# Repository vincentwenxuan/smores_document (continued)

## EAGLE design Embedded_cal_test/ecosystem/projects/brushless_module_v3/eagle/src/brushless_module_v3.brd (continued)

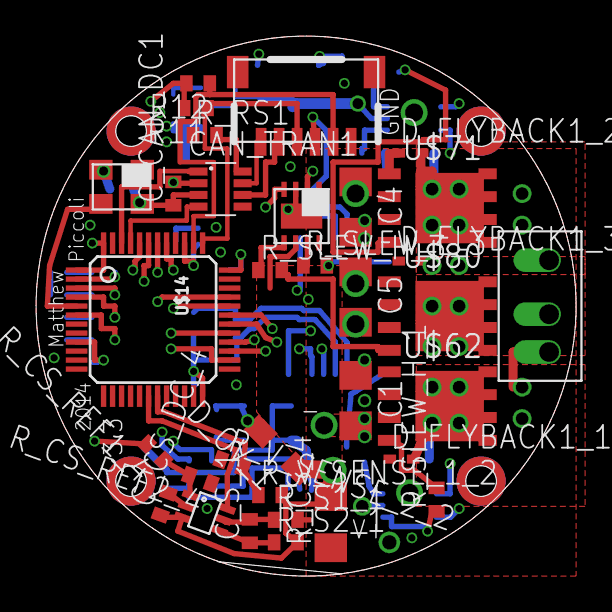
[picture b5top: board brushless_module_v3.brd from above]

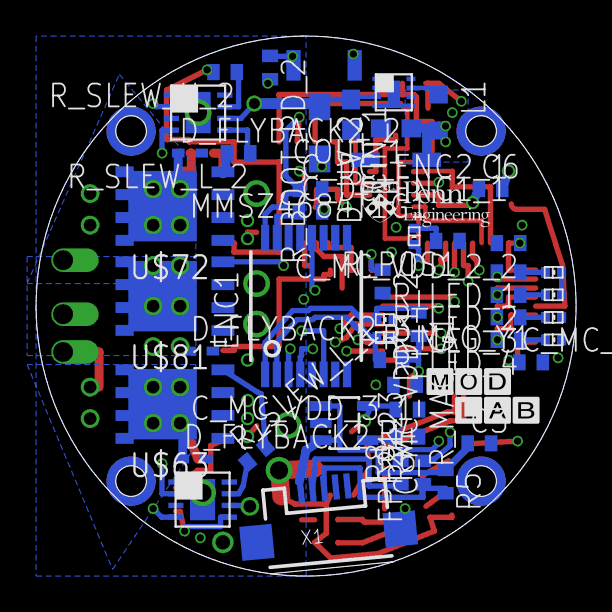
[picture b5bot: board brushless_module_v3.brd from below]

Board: 4 copper layers, 30.0 x 30.0 mm, 84 parts (51 on the bottom side), 63 nets.

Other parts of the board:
U$6: MODLAB
U$12: PENN_ENGINEERING

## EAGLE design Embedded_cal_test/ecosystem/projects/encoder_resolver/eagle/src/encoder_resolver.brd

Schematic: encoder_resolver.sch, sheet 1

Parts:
C_MC_VDDA_1: 100nF; C0603
C_MC_VDD_1_1: 4.7uF; C0603
C_MC_VDD_2_1: 100nF; C0603
IC7: STM32F373CC; LQFP48
LED1, LED2, LED3, LED4: LEDCHIPLED_0603; CHIPLED_0603
OSC1: FOX924B; 4-SMD_5X3.2
R_BOOT_PU_1: 1k; R0603
R_LED_1, R_LED_3, R_LED_4, R_LED_5: 1k; R0603
R_NRST_PU_1: 1k; R0603
R_V_SENSE_1_1: 88.7kΩ; R0603
R_V_SENSE_2_1: 20kΩ; R0603
SW1: B3U

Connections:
16MHZ_3V3: IC7.5 (PF0-OSC_IN-I2C2SDA+), OSC1.P$3 (OUTPUT)
+3V3: C_MC_VDDA_1.1, C_MC_VDD_1_1.1, C_MC_VDD_2_1.1, IC7.1 (VBAT), IC7.9 (VDDA-VREF+), IC7.17 (VDD_2), IC7.24 (VDDSD), IC7.25 (VREFSD), IC7.48 (VDD_1), LED1.A, LED2.A, LED3.A, LED4.A, OSC1.P$4 (VCC), R_NRST_PU_1.1, SW1.P$2; also elsewhere on the board
BOOT0_1: IC7.44 (BOOT0), R_BOOT_PU_1.1, SW1.P$1
D+1: IC7.33 (PA12-USART1RTS/USBDP/SPI1SCK); also elsewhere on the board
D-1: IC7.32 (PA11-USART1CTS/USBDM/SPI2NSS/SPI1NSS); also elsewhere on the board
ENC_CLK_1: IC7.11 (PA1-USART2RTS/ADC1/SPI3SCK/TIM2CH2); also elsewhere on the board
ENC_CSN_1: IC7.10 (PA0-USART2CTS/ADC0); also elsewhere on the board
ENC_MISO_1: IC7.12 (PA2-USART2TX/ADC2/SPI3MISO/TIM2CH3); also elsewhere on the board
E_R1-R2_MICRO: IC7.16 (PA6-SPI1MISO/ADC6/TIM3CH1); also elsewhere on the board
E_S1-S3_MICRO: IC7.14 (PA4-SPI1NSS/ADC4/SPI3NSS/USART2CK); also elsewhere on the board
E_S2-S4_MICRO: IC7.15 (PA5-SPI1SCK/ADC5); also elsewhere on the board
GND: C_MC_VDDA_1.2, C_MC_VDD_1_1.2, C_MC_VDD_2_1.2, IC7.8 (VSSA-VREF-), IC7.23 (VSSD-VREFSD-), IC7.47 (VSS_1), OSC1.P$2 (GND), R_BOOT_PU_1.2, R_V_SENSE_2_1.1; also elsewhere on the board
INDEX1: IC7.6 (PF1-OSC_OUT-I2C2SCL+); also elsewhere on the board
MAGDEC1: IC7.41 (PB5-SPI1MOSI/SPI3MOSI); also elsewhere on the board
unnamed: LED1.C, R_LED_1.2
unnamed: IC7.18 (PB0-ADC8/SPI1MOSI/TIM3CH3), R_V_SENSE_1_1.1, R_V_SENSE_2_1.2
unnamed: IC7.38 (PA15-I2C1SCL+), R_LED_1.1
unnamed: LED2.C, R_LED_3.2
unnamed: IC7.37 (PA14-I2C1SDA+), R_LED_3.1
unnamed: LED4.C, R_LED_4.2
unnamed: LED3.C, R_LED_5.2
unnamed: IC7.29 (PA8-USART1CK/SPI2SCK/MCO), R_LED_4.1
unnamed: IC7.30 (PA9-USART1TX/SPI2MISO), R_LED_5.1
NRST_1: IC7.7 (NRST), R_NRST_PU_1.2
POS_PWM1: IC7.13 (PA3-USART2RX/ADC3/SPI3MOSI/TIM2CH4); also elsewhere on the board
QEPA1: IC7.42 (PB6-I2C1SCL+); also elsewhere on the board
QEPB1: IC7.43 (PB7-I2C1SDA+); also elsewhere on the board
V+: R_V_SENSE_1_1.2; also elsewhere on the board

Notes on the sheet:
Delete if more than one of this sheet

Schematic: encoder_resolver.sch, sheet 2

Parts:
R1: 22Ω; R0603
R2: 1.5k; R0603
R3: 22; R0603
X1: USB-MICROB

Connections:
+5V/1: R2.1, X1.VBUS; also elsewhere on the board
D+1: R1.2; also elsewhere on the board
D+_IN_1: R1.1, R2.2, X1.D+
D-1: R3.2; also elsewhere on the board
D-_IN_1: R3.1, X1.D-
GND: X1.GND, X1.MT1 (GND), X1.MT2 (GND); also elsewhere on the board

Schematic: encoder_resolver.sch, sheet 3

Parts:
C_DC_ENC1_1: 10uF; C0603
C_DC_ENC2_1: 100nF; C0603
ENC1: AS5040; SSOP16
LED_MAG_G1: G; CHIP-LED0603
LED_POS1: B; CHIP-LED0603
R_MAG_G1: 1kΩ; R0603
R_POS1: 1kΩ; R0603

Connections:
+3V3: C_DC_ENC2_1.1, ENC1.16 (VDD5V), R_MAG_G1.2; also elsewhere on the board
ENC_3V3_1: C_DC_ENC1_1.1, ENC1.15 (VDD3V3)
ENC_CLK_1: ENC1.10 (CLK); also elsewhere on the board
ENC_CSN_1: ENC1.11 (CSN); also elsewhere on the board
ENC_MISO_1: ENC1.9 (D0); also elsewhere on the board
GND: C_DC_ENC1_1.2, C_DC_ENC2_1.2, ENC1.7 (VSS), ENC1.8 (PROG), LED_MAG_G1.C, LED_POS1.C; also elsewhere on the board
INDEX1: ENC1.6 (INDEX_W); also elsewhere on the board
MAGDEC1: ENC1.2 (MAGDEC); also elsewhere on the board
MAGINC1: ENC1.1 (MAGINC), LED_MAG_G1.A, R_MAG_G1.1
unnamed: LED_POS1.A, R_POS1.2
POS_PWM1: ENC1.12 (PWN), R_POS1.1; also elsewhere on the board
QEPA1: ENC1.3 (A_LSB_U); also elsewhere on the board
QEPB1: ENC1.4 (B_DIR_V); also elsewhere on the board

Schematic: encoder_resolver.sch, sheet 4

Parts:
CIN1_1, CIN2_1: 10µF; C0805
COUT1_1, COUT2_1: 22µF; C0603
C_BOOST1: 22nF; C0603
L_REG1: 4.7µH; VLC5045
SW_REG1: MCP16323; QFN16

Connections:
+5V: COUT1_1.1, COUT2_1.1, L_REG1.2, SW_REG1.5 (VFB); also elsewhere on the board
BOOST1: C_BOOST1.1, SW_REG1.10 (BOOST)
GND: CIN1_1.2, CIN2_1.2, COUT1_1.2, COUT2_1.2, SW_REG1.4 (SGND), SW_REG1.14 (PGND), SW_REG1.15 (PGND), SW_REG1.TH (SGND); also elsewhere on the board
SW1: C_BOOST1.2, L_REG1.1, SW_REG1.1 (SW), SW_REG1.12 (SW), SW_REG1.13 (SW), SW_REG1.16 (SW)
V+: CIN1_1.1, CIN2_1.1, SW_REG1.2 (VIN), SW_REG1.3 (VIN), SW_REG1.11 (VIN); also elsewhere on the board

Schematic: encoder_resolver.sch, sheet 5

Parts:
C_BYP_IN_1: 10µF; C1206
C_BYP_OUT_1: 10µF; C0603
U$6: LD111733; SOT-223

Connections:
+3V3: C_BYP_OUT_1.1, U$6.2 (VOUT), U$6.4 (VOUT); also elsewhere on the board
+5V: C_BYP_IN_1.1, U$6.3 (VIN); also elsewhere on the board
GND: C_BYP_IN_1.2, C_BYP_OUT_1.2, U$6.1 (GND); also elsewhere on the board

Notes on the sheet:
Default is +3V3, change here!

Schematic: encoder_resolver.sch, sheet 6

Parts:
C2: 100nF; C0603
C3: 10uF; C0603
D_OV_1: PMEG2005EJ,115; SOD323-W
FPF: FPF; SOT23-5L
R4: 1MΩ; R0603
R6: 604Ω; R0603

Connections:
+5V: C2.1, D_OV_1.C; also elsewhere on the board
+5V/1: C3.1, FPF.1 (VIN), FPF.3 (ON); also elsewhere on the board
GND: C2.2, C3.2, FPF.2 (GND), R4.1, R6.1; also elsewhere on the board
LOAD_ISET_1: FPF.4 (ISET), R6.2
unnamed: D_OV_1.A, FPF.5 (VOUT), R4.2

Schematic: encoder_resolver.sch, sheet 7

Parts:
JP1: PINHD-1X6; 1X06
P_POWER: PINHD-1X2; 1X02

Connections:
E_R1: JP1.1; also elsewhere on the board
E_R2: JP1.2; also elsewhere on the board
E_S1: JP1.5; also elsewhere on the board
E_S2: JP1.3; also elsewhere on the board
E_S3: JP1.6; also elsewhere on the board
E_S4: JP1.4; also elsewhere on the board
GND: P_POWER.2; also elsewhere on the board
V+: P_POWER.1; also elsewhere on the board

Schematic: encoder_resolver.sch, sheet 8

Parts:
C1, C4, C7, C8, C10, C11: 1µF; C0603
C5: 1nF; C0603
C6, C9: 100pF; C0603
IC1: AD8544RU; TSSOP14
R5, R11: 100kΩ; R0603
R7, R8, R15, R17, R19, R21: 10kΩ; R0603
R9: 4.7kΩ; R0603
R10, R14, R18, R22: 1kΩ; R0603
R12, R13: 22kΩ; R0603
R16, R20: 12.7kΩ; R0603

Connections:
+3V3: R7.2; also elsewhere on the board
E_R1: C1.1; also elsewhere on the board
E_R1-R2_MICRO: C5.1, R14.1; also elsewhere on the board
E_R2: C4.1; also elsewhere on the board
E_S1: C10.1, R22.1; also elsewhere on the board
E_S1-S3_MICRO: R19.2; also elsewhere on the board
E_S2: C7.1, R18.1; also elsewhere on the board
E_S2-S4_MICRO: R15.2; also elsewhere on the board
E_S3: C11.1, R22.2; also elsewhere on the board
E_S4: C8.1, R18.2; also elsewhere on the board
GND: C5.2, C6.2, C8.2, C9.2, C11.2, IC1.11 (V-), R8.1, R17.1, R21.1; also elsewhere on the board
unnamed: IC1.3 (IN+), R7.1, R8.2
unnamed: IC1.2 (IN-), R9.2
unnamed: C4.2, R5.1, R10.2
unnamed: C1.2, R10.1, R11.1
unnamed: IC1.5 (IN+), R5.2, R13.2
unnamed: IC1.6 (IN-), R11.2, R12.1
unnamed: IC1.7 (OUT), R12.2, R14.2
unnamed: C6.1, IC1.10 (IN+), R15.1
unnamed: IC1.9 (IN-), R16.1, R17.2
unnamed: C7.2, IC1.8 (OUT), R16.2
unnamed: C9.1, IC1.12 (IN+), R19.1
unnamed: IC1.13 (IN-), R20.1, R21.2
unnamed: C10.2, IC1.14 (OUT), R20.2
V+: IC1.4 (V+); also elsewhere on the board
VCC/2: IC1.1 (OUT), R9.1, R13.1

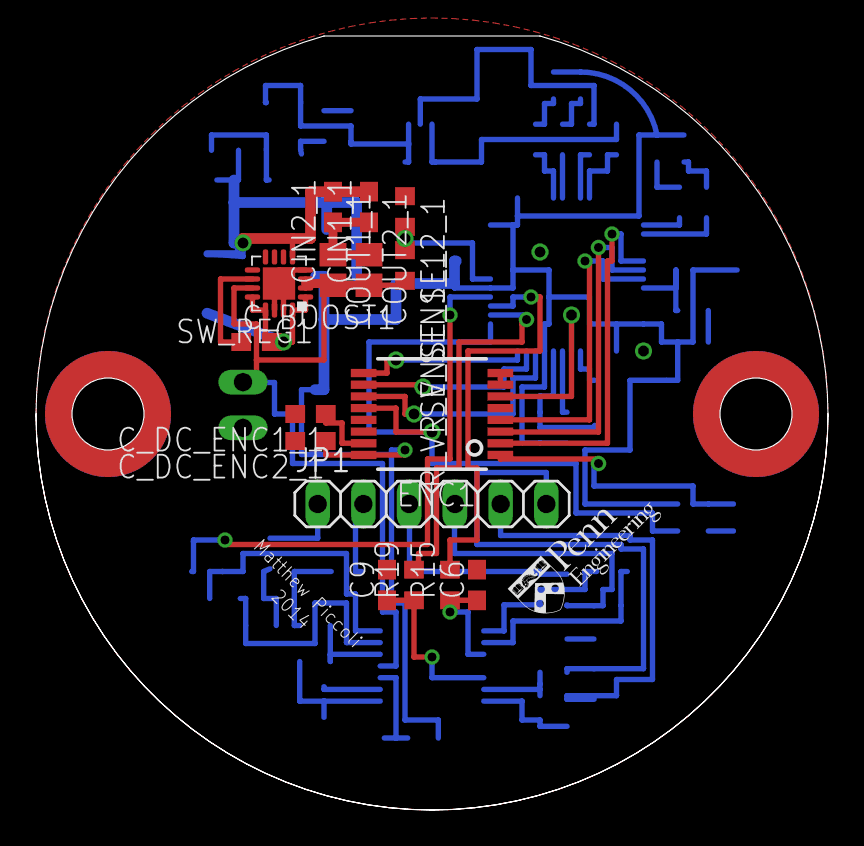
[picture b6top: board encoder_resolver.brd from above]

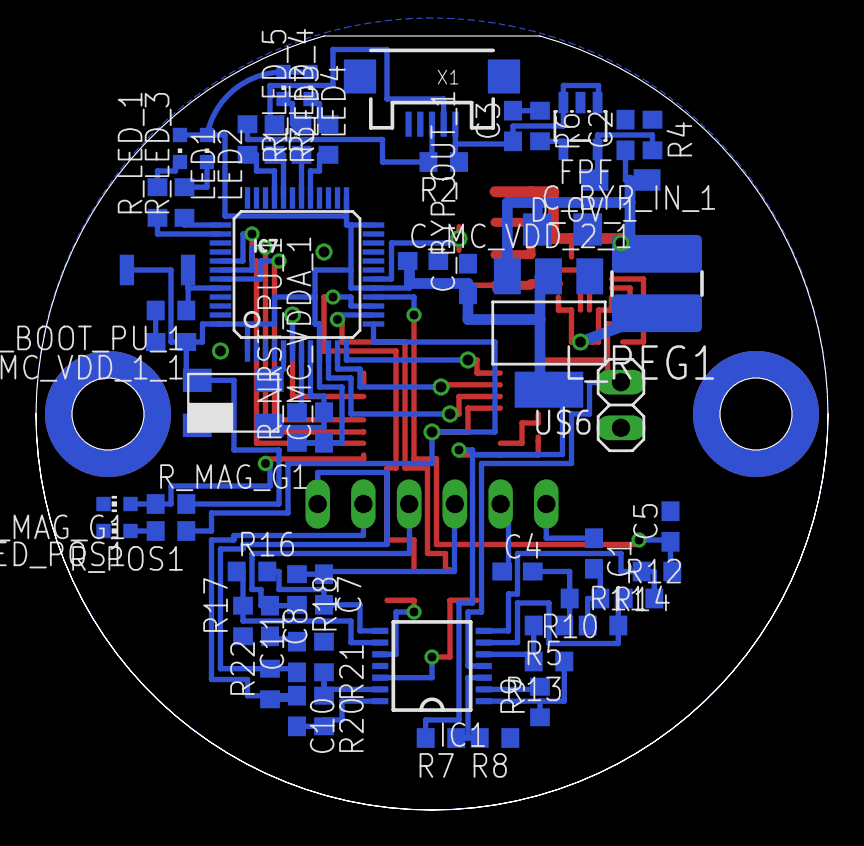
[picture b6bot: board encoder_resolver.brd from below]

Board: 2 copper layers, 44.0 x 43.0 mm, 75 parts (58 on the bottom side), 59 nets.

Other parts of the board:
U$11: PENN_ENGINEERING

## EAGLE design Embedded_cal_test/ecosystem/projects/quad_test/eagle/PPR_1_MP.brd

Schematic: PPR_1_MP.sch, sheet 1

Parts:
C_MC_VDDA_1: 100nF; C0402
C_MC_VDD_1_1: 4.7uF; C0402
C_MC_VDD_2_1: 100nF; C0402
C_NRST_LP_1: 4.7uF; C0603K
IC5: SN74LVC2G14DCKR; DCK
IC6: SN74LVC1G373DCKR; DCK
IC7: STM32F373CC; LQFP48
LED_RST_1: orange; CHIPLED_0603
LED_RST_4: white; CHIPLED_0603
LED_STAT_1: red; CHIPLED_0603
LED_STAT_2: green; CHIPLED_0603
LED_STAT_3: blue; CHIPLED_0603
OSC1: FOX924B; 4-SMD_5X3.2
R_NRST_LP_1: 220k; R0402
R_NRST_PU_1: 1k; R0402
R_RST_LED_1: 1k; R0402
R_STAT_LED_1, R_STAT_LED_2, R_STAT_LED_3, R_STAT_LED_4: 1k; R0402
SW1: B3U

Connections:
16MHZ_3V3: IC7.5 (PF0-OSC_IN-I2C2SDA+), OSC1.P$3 (OUTPUT); also elsewhere on the board
+3V3: C_MC_VDDA_1.1, C_MC_VDD_1_1.1, C_MC_VDD_2_1.1, IC5.P$5 (V+), IC6.P$5 (V+), IC7.1 (VBAT), IC7.9 (VDDA-VREF+), IC7.17 (VDD_2), IC7.24 (VDDSD), IC7.25 (VREFSD), IC7.48 (VDD_1), OSC1.P$4 (VCC), R_NRST_PU_1.1; also elsewhere on the board
BOOT0_1: IC5.P$6 (1Y), IC6.P$3 (D), IC7.44 (BOOT0)
D+1: IC7.33 (PA12-USART1RTS/USBDP/SPI1SCK); also elsewhere on the board
D-1: IC7.32 (PA11-USART1CTS/USBDM/SPI2NSS/SPI1NSS); also elsewhere on the board
GND: C_MC_VDDA_1.2, C_MC_VDD_1_1.2, C_MC_VDD_2_1.2, C_NRST_LP_1.2, IC5.P$2 (GND), IC6.P$2 (GND), IC6.P$6 (_OE), IC7.8 (VSSA-VREF-), IC7.23 (VSSD-VREFSD-), IC7.47 (VSS_1), OSC1.P$2 (GND), R_RST_LED_1.1, R_STAT_LED_1.1, R_STAT_LED_2.1, R_STAT_LED_3.1, R_STAT_LED_4.1, SW1.P$1; also elsewhere on the board
IMU_SCL_1: IC7.38 (PA15-I2C1SCL+); also elsewhere on the board
IMU_SDA_1: IC7.37 (PA14-I2C1SDA+); also elsewhere on the board
LED_RST_1_1: IC6.P$4 (Q), LED_RST_1.A
LED_RST_2_1: LED_RST_1.C, R_RST_LED_1.2
LED_RST_2_2: LED_STAT_1.C, R_STAT_LED_1.2
LED_RST_2_3: LED_STAT_2.C, R_STAT_LED_2.2
LED_RST_2_5: LED_RST_4.C, R_STAT_LED_4.2
LED_STAT_2_3: LED_STAT_3.C, R_STAT_LED_3.2
LE_1: IC5.P$4 (2Y), IC6.P$1 (LE)
unnamed: IC7.20 (PB2), LED_STAT_3.A
unnamed: IC7.18 (PB0-ADC8/SPI1MOSI/TIM3CH3), LED_STAT_1.A
unnamed: IC7.19 (PB1-ADC9/TIM3CH4), LED_STAT_2.A
unnamed: IC7.21 (PE8), LED_RST_4.A
NRST_1: IC5.P$3 (2A), IC7.7 (NRST), R_NRST_LP_1.2, R_NRST_PU_1.2, SW1.P$2
NRST_LP_1: C_NRST_LP_1.1, IC5.P$1 (1A), R_NRST_LP_1.1
PWM_1: IC7.40 (PB4-SPI1MISO/SPI3MISO); also elsewhere on the board
PWM_2: IC7.41 (PB5-SPI1MOSI/SPI3MOSI); also elsewhere on the board
PWM_3: IC7.42 (PB6-I2C1SCL+); also elsewhere on the board
PWM_4: IC7.43 (PB7-I2C1SDA+); also elsewhere on the board
ZB_IRQ_1: IC7.22 (PE9); also elsewhere on the board
ZB_MISO_1: IC7.26 (PB14-SPI2MISO); also elsewhere on the board
ZB_MOSI_1: IC7.27 (PB15-SPI2MOSI); also elsewhere on the board
ZB_SCLK_1: IC7.28 (PD8-SPI2SCK); also elsewhere on the board

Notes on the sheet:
Latch D > Q
Inverter (not gate)
Push reset, hold boot
Delete if more than one of this sheet
If using A2D

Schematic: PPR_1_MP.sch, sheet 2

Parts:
BALUN1: 0896FB15A0100
CB1, CB2, CB3, CB4: 1µF; C0603
C_RF_CU1_1, C_RF_CU2_1: 68µF; C0603
C_ZB_XTRF1: 100nF; C0603
JP1: Whip; 1X01M
RADIO1: AT86RF; QFNN32
R_CLK_VDIV1_1: 5k6; R0603
R_CLK_VDIV2_1: 1k; R0603

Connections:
16MHZ_0V5_1: C_ZB_XTRF1.2, R_CLK_VDIV1_1.1, R_CLK_VDIV2_1.2
16MHZ_0V5_AC1: C_ZB_XTRF1.1, RADIO1.26 (XTAL1)
16MHZ_3V3: R_CLK_VDIV1_1.2; also elsewhere on the board
+3V3: CB2.1, CB4.1, RADIO1.15 (DEVDD), RADIO1.28 (EVDD); also elsewhere on the board
ANT1: BALUN1.1 (UNBALANCED), JP1.1
GND: BALUN1.2 (GND), BALUN1.5 (GND), BALUN1.6 (GND), CB1.2, CB2.2, CB3.2, CB4.2, RADIO1.3 (AVSS), RADIO1.6 (AVSS), RADIO1.7 (DVSS), RADIO1.12 (DVSS), RADIO1.16 (DVSS), RADIO1.18 (DVSS), RADIO1.21 (DVSS), RADIO1.23 (\SEL), RADIO1.27 (AVSS), RADIO1.30 (AVSS), RADIO1.31 (AVSS), RADIO1.32 (AVSS), RADIO1.EXP (AVSS), R_CLK_VDIV2_1.1; also elsewhere on the board
ZB_AVDD1: CB1.1, RADIO1.29 (AVDD)
ZB_BAL1_1: BALUN1.3 (BALANCED1), C_RF_CU1_1.2
ZB_BAL2_1: BALUN1.4 (BALANCED2), C_RF_CU2_1.2
ZB_DVDD1: CB3.1, RADIO1.13 (DVDD), RADIO1.14 (DVDD)
ZB_IRQ_1: RADIO1.24 (IRQ); also elsewhere on the board
ZB_MISO_1: RADIO1.20 (MISO); also elsewhere on the board
ZB_MOSI_1: RADIO1.22 (MOSI); also elsewhere on the board
ZB_RFN1: C_RF_CU2_1.1, RADIO1.4 (RFP)
ZB_RFP1: C_RF_CU1_1.1, RADIO1.5 (RFN)
ZB_SCLK_1: RADIO1.19 (SCLK); also elsewhere on the board

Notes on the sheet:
Connect ZB_SEL_x to the cable select pin
Connect ZB_MOSI_x to MOSI RPx pin
Connect ZB_SCLK_x to the SPI clock PRx pin
Connect ZB_MISO_x to MISO PRIx pin
Connect ZB_IRQ_x to the Interrupt Request pin
Equal length, short
Short

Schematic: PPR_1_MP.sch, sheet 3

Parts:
CN2: FCI-10103594-0001LF
R1, R3: 22Ω; R0402
R2: 1.5k; R0402

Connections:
D+1: R1.2; also elsewhere on the board
D+_IN_1: CN2.3 (D+), R1.1, R2.2
D-1: R3.2; also elsewhere on the board
D-_IN_1: CN2.2 (D-), R3.1
GND: CN2.5 (GND); also elsewhere on the board
V+: CN2.1 (VCC), R2.1; also elsewhere on the board

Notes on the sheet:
Connect VBUSx to the VBUS pin on the microcontroller
Connect D+x to the D+ pin on the microcontroller
Connect D-x to the D- pin on the microcontroller
The maximum capacitance on VBUS is 10µF and minimum is 1µF
IF DRAWING POWER FROM USB, CHECK THE VOLTAGE REGULATOR FOR CAPACITANCE

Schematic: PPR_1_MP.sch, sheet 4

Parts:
JP11: PINHD-1X2; 1X02
Q1: ZXMN3A01F; SOT23-3
R_LIM_1: 330Ω; R0805

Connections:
DRIVER_OUT_1: JP11.2, Q1.3 (D)
GATE_1: Q1.1 (G), R_LIM_1.2
GND: Q1.2 (S); also elsewhere on the board
PWM_1: R_LIM_1.1; also elsewhere on the board
V+: JP11.1; also elsewhere on the board

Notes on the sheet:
Connect PWM_x to the PWMxx microcontroller pin
Connect DRIVER_OUT_X to the load

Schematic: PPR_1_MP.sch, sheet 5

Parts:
JP2: PINHD-1X2; 1X02
Q2: ZXMN3A01F; SOT23-3
R_LIM_2: 330Ω; R0805

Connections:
DRIVER_OUT_2: JP2.2, Q2.3 (D)
GATE_2: Q2.1 (G), R_LIM_2.2
GND: Q2.2 (S); also elsewhere on the board
PWM_2: R_LIM_2.1; also elsewhere on the board
V+: JP2.1; also elsewhere on the board

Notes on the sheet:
Connect PWM_x to the PWMxx microcontroller pin
Connect DRIVER_OUT_X to the load

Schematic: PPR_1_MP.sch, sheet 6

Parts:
JP3: PINHD-1X2; 1X02
Q3: ZXMN3A01F; SOT23-3
R_LIM_3: 330Ω; R0805

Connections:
DRIVER_OUT_3: JP3.2, Q3.3 (D)
GATE_3: Q3.1 (G), R_LIM_3.2
GND: Q3.2 (S); also elsewhere on the board
PWM_3: R_LIM_3.1; also elsewhere on the board
V+: JP3.1; also elsewhere on the board

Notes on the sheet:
Connect PWM_x to the PWMxx microcontroller pin
Connect DRIVER_OUT_X to the load

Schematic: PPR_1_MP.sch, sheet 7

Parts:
JP4: PINHD-1X2; 1X02
Q4: ZXMN3A01F; SOT23-3
R_LIM_4: 330Ω; R0805

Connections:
DRIVER_OUT_4: JP4.2, Q4.3 (D)
GATE_4: Q4.1 (G), R_LIM_4.2
GND: Q4.2 (S); also elsewhere on the board
PWM_4: R_LIM_4.1; also elsewhere on the board
V+: JP4.1; also elsewhere on the board

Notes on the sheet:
Connect PWM_x to the PWMxx microcontroller pin
Connect DRIVER_OUT_X to the load

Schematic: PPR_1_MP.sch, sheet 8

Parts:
C_BYP_IN_1: 10µF; C1206
C_BYP_OUT_1: 10µF; C0603
REG: LD1117XX; SOT-223

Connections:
+3V3: C_BYP_OUT_1.1, REG.2 (VOUT), REG.4 (VOUT2); also elsewhere on the board
GND: C_BYP_IN_1.2, C_BYP_OUT_1.2, REG.1 (GND); also elsewhere on the board
V+: C_BYP_IN_1.1, REG.3 (VIN); also elsewhere on the board

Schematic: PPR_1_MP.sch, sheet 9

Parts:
C_IMU_B_1: .1uF; 0402-CAP
C_IMU_CP_1: 2.2nF; 0402-CAP
C_IMU_FILT_1: .1uF; 0402-CAP
I2C_PULLUP_1, I2C_PULLUP_2: 10k; R0402
U5: TESTING_MPU-6050-1; TESTING_QFN-24-4MM2
VLOGIC_BYPASS_1: 10nF; 0402-CAP

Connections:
+3V3: C_IMU_B_1.2, I2C_PULLUP_1.2, I2C_PULLUP_2.2, U5.8 (VLOGIC), U5.13 (VDD), VLOGIC_BYPASS_1.2; also elsewhere on the board
CPOUT_1: C_IMU_CP_1.2, U5.20 (CPOUT)
GND: C_IMU_B_1.1, C_IMU_CP_1.1, C_IMU_FILT_1.1, U5.1 (CLKIN), U5.9 (AD0), U5.11 (FSYNC), U5.18 (GND), VLOGIC_BYPASS_1.1; also elsewhere on the board
IMU_IRQ_1: U5.12 (INT)
IMU_SCL_1: I2C_PULLUP_1.1, U5.23 (SCL); also elsewhere on the board
IMU_SDA_1: I2C_PULLUP_2.1, U5.24 (SDA); also elsewhere on the board
REGOUT_1: C_IMU_FILT_1.2, U5.10 (REGOUT)

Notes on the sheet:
I2C ADDR Select

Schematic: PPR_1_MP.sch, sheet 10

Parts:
C_IMU_DC_1: .1uF; 0402-CAP
U$12: MS5611-01BA

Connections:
+3V3: C_IMU_DC_1.2, U$12.1 (VDD), U$12.2 (PS); also elsewhere on the board
GND: C_IMU_DC_1.1, U$12.3 (GND), U$12.4 (CSB1), U$12.5 (CSB2); also elsewhere on the board
IMU_SCL_1: U$12.8 (SCLK); also elsewhere on the board
IMU_SDA_1: U$12.7 (SDI/SDA); also elsewhere on the board

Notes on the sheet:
Connect PS_SDA_x to microcontroller SDA pin
Connect PS_SCL_x to microcontroller SCL pin

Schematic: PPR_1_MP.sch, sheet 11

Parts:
JP10: PINHD-1X2; 1X02

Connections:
GND: JP10.2; also elsewhere on the board
V+: JP10.1; also elsewhere on the board

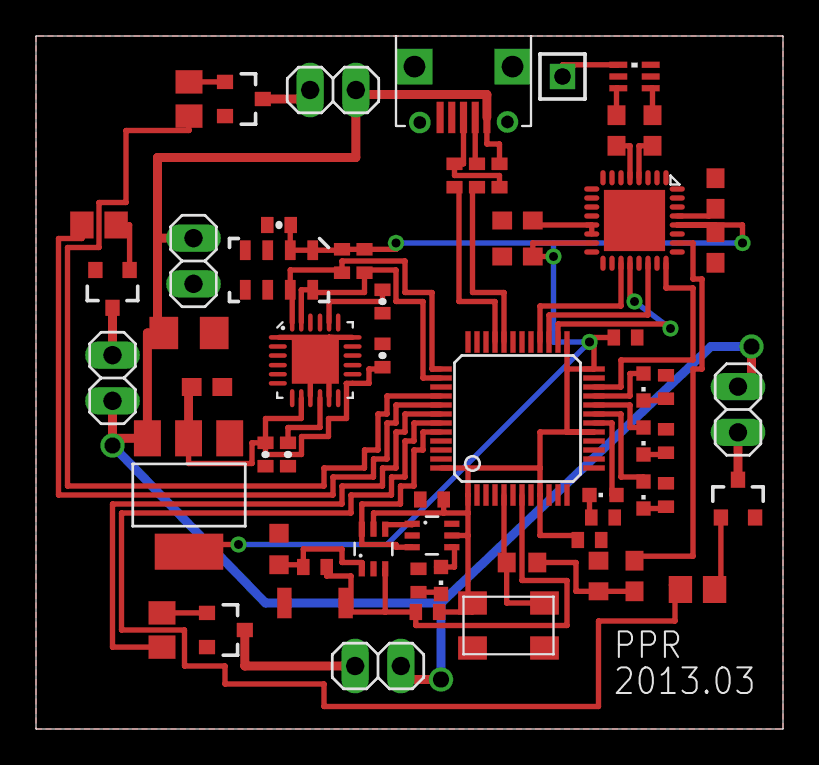
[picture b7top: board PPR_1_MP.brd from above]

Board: 2 copper layers, 41.5 x 38.5 mm, 62 parts (0 on the bottom side), 51 nets.

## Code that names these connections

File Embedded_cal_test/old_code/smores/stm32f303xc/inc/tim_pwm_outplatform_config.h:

/*
Author Chaitanya Bhargava (cbhar@seas.upenn.edu)
Settings for TIMER PWM OUT usage on the STM32F303
mGeneral includes all the ST library files and the wait functions
For simple control of motors
*/
/* FOR NOW CONFIGURED TO DRIVE 4 MOTORS ON THE SMORES*/
#ifdef	__cplusplus
extern "C" {
#endif
/*-------------TIMA, PA8-----------------*/
#define TIMA			TIM1
#define TIMA_RCC		RCC_APB2Periph_TIM1
#define TIMA_PORT		GPIOA
#define TIMA_PIN		GPIO_Pin_8
#define TIMA_PIN_SOURCE GPIO_PinSource8
#define TIMA_AF			GPIO_AF_6

/*-------------TIMB, PA9-----------------*/
#define TIMB			TIM2
#define TIMB_RCC		RCC_APB1Periph_TIM2
#define TIMB_PORT		GPIOA
#define TIMB_PIN		GPIO_Pin_9
#define TIMB_PIN_SOURCE GPIO_PinSource9
#define TIMB_AF			GPIO_AF_10

/*-------------TIMC, PB14-----------------*/
#define TIMC			TIM15
#define TIMC_RCC		RCC_APB2Periph_TIM15
#define TIMC_PORT		GPIOB
#define TIMC_PIN		GPIO_Pin_14
#define TIMC_PIN_SOURCE GPIO_PinSource14
#define TIMC_AF			GPIO_AF_1

/*-------------TIMD, PA1-----------------*/
#define TIMD			TIM2
#define TIMD_RCC		RCC_APB1Periph_TIM2
#define TIMD_PORT		GPIOA
#define TIMD_PIN		GPIO_Pin_1
#define TIMD_PIN_SOURCE GPIO_PinSource1
#define TIMD_AF			GPIO_AF_1

/*-------------M1 Direction, PB2-----------------*/
#define MA_DIR_PORT		GPIOB
#define MA_DIR_PIN		GPIO_Pin_2

/*-------------M2 Direction, PA10-----------------*/
#define MB_DIR_PORT		GPIOA
#define MB_DIR_PIN		GPIO_Pin_10
	
/*-------------M3 Direction, PB15-----------------*/
#define MD_DIR_PORT		GPIOB
#define MD_DIR_PIN		GPIO_Pin_15

/*-------------M4 Direction, PA0-----------------*/
#define MC_DIR_PORT		GPIOA
#define MC_DIR_PIN		GPIO_Pin_0


#ifdef	__cplusplus
}
#endif

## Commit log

2015-06-03 upload file initially
2015-06-03 Create REA
2015-06-03 test
2015-06-03 test2
2015-06-03 format adjustment in main_verbose.cpp
2015-06-03 testing
2015-06-03 main2
2015-06-03 nothing, just did some organize
2015-06-03 added some TWX comment
2015-06-04 added more comment and questions on main_verbose.cpp
2015-06-04 updated some comment
2015-06-16 calibraion test
2015-06-16 atmega cali test
2015-06-17 Beta
2015-06-17 comment out coil
2015-06-17 modified mainc and maincpp
2015-06-17 fasdjladjadasjd
2015-06-17 modified to be flashable
2015-06-17 stm32
2015-06-17 message type
2015-06-17 motor
2015-06-17 motor works
2015-06-17 add a doc about after-test
2015-06-18 restore atm_cali.c
2015-06-23 connection fine
2015-06-25 nealy done
2015-06-30 tested with eeprom
2015-06-30 TWI_slave update
2015-06-30 readme
2015-07-15 manipulation
2015-07-15 seperate commands to control the faces one by one
2015-07-20 fully functionalized auto calibration except wiper_encoder.h part
2015-08-31 Modify wiper_encoder.c
2015-08-31 readme update
